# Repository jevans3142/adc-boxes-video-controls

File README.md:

# ADC Theatre - Control Boxes Video Switchers

This repository hosts the hardware (in the form of KiCad schematics, PCB layouts, 3D print files, and metalwork cutting outines) and 
firmware (in the form of C code) of the [ADC Theatre's](https://www.adctheatre.com) Control Boxes Video Switchers. These are a pair of control panels mounted in each control box which 
provides remote control of a Blackmagic Design Videohub SDI switcher via Ethernet.

## Features
* Each panel controls a single video output on the switcher, with six sources 
* Panels have steel panel fronts and backs, with a 3D printed case around them
* An additional steel plate mounts the assembly to a VESA mount behind a screen to drop the panel neatly under the screen

## Configuration

Although some things such as number of buttons etc are fixed in hardware, some aspects can be customised via a text file 
on a microSD card read at boot. This provides the ADC with the ability to reconfigure for example which sources are availible on the panel without having to recompile firmware (as long as the physical buttons are relabeled of course!)

Items which can be configured: 
* Which router inputs are used as sources for each of the destinations 
* IP address of the router

## Compilation
The microcontroller used is an ESP32 on an Olimex ESP32-PoE-ISO board. After standard installation of the esp-idf FreeRTOS toolchain, currently building on v5.1.1 as a stable version with the configuration included in the src folder (ie. when building do not run the idf.py set-target esp32 command as directed in the esp-idf Getting Started instructions to set up the default build config - just go straight to idf.py build)

## Hardware
Each panel requires the following components: 
* A Olimex ESP32-PoE-ISO board
* A custom PCB 'main-board' to break out the button/LED connections
* A 3D printed case, which various heat-fit standoffs need to be sunk into to mount the main-board PCB and front/back panels
* A front panel consisting of a laser cut steel panel with buttons/LEDs mounted in; this also has a label strip. A 3D printed version is in the repo, but there is an off-the-shelf part that can be used too 
* A back panel with another 3D printed part used as an SD card cover
* A VESA mounting steel plate 

## Copyright
Copyright (c) 2021-2024 John Evans and contributors.
The ADC Control Boxes Video Switcher hardware and firmware is released under Version 3 of the GNU General Public License.
See the LICENSE file for full details.

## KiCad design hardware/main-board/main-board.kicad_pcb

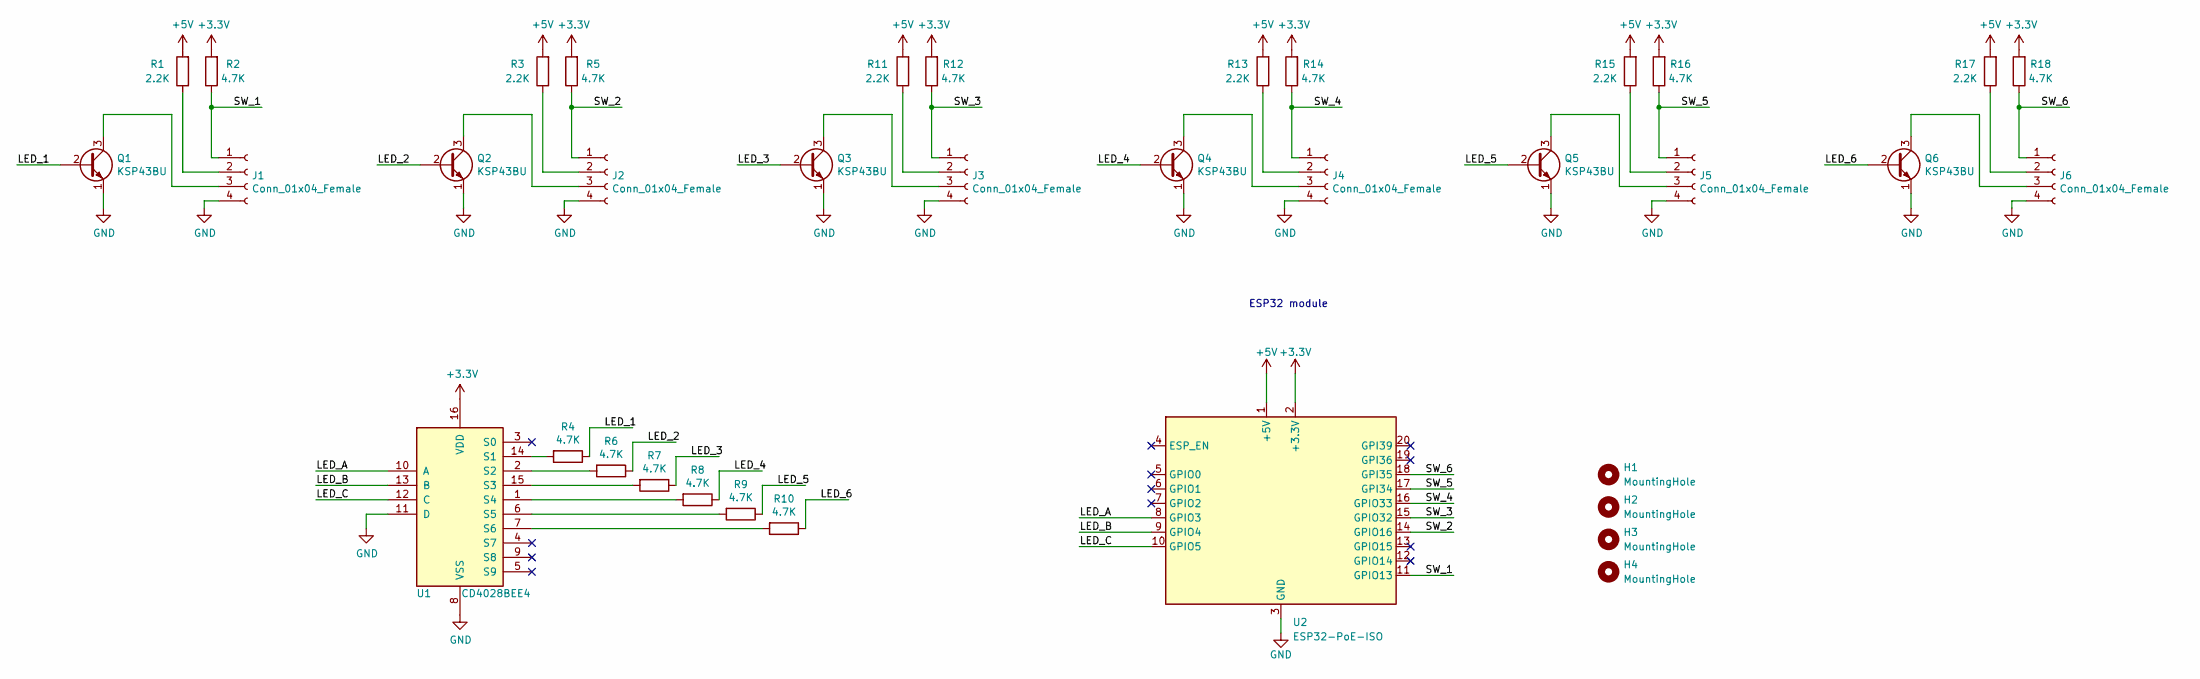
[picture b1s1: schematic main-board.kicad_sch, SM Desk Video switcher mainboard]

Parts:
H1, H2, H3, H4: MountingHole; MountingHole_3.2mm_M3
J1, J2, J3, J4, J5, J6: Conn_01x04_Female; PinHeader_1x04_P2.54mm_Vertical
Q1, Q2, Q3, Q4, Q5, Q6: KSP43BU; TO-92_Inline_Wide
R1, R3, R11, R13, R15, R17: 2.2K; R_Axial_DIN0207_L6.3mm_D2.5mm_P10.16mm_Horizontal
R2, R4, R5, R6, R7, R8, R9, R10, R12, R14, R16, R18: 4.7K; R_Axial_DIN0207_L6.3mm_D2.5mm_P10.16mm_Horizontal
U1: CD4028BEE4; DIP-16_W7.62mm_Socket
U2: ESP32-PoE-ISO; Olimex_ESP32_PoE_ISO

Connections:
+3V3: R2.2, R5.2, R12.2, R14.2, R16.2, R18.2, U1.16 (VDD), U2.2 (+3.3V)
+5V: R1.2, R3.2, R11.2, R13.2, R15.2, R17.2, U2.1 (+5V)
/LED_1: Q1.2 (B), R4.1
/LED_2: Q2.2 (B), R6.1
/LED_3: Q3.2 (B), R7.1
/LED_4: Q4.2 (B), R8.1
/LED_5: Q5.2 (B), R9.1
/LED_6: Q6.2 (B), R10.1
/LED_A: U1.10 (A), U2.8 (GPIO3)
/LED_B: U1.13 (B), U2.9 (GPIO4)
/LED_C: U1.12 (C), U2.10 (GPIO5)
/SW_1: J1.1, R2.1, U2.11 (GPIO13)
/SW_2: J2.1, R5.1, U2.14 (GPIO16)
/SW_3: J3.1, R12.1, U2.15 (GPIO32)
/SW_4: J4.1, R14.1, U2.16 (GPIO33)
/SW_5: J5.1, R16.1, U2.17 (GPI34)
/SW_6: J6.1, R18.1, U2.18 (GPI35)
GND: J1.4, J2.4, J3.4, J4.4, J5.4, J6.4, Q1.1 (E), Q2.1 (E), Q3.1 (E), Q4.1 (E), Q5.1 (E), Q6.1 (E), U1.8 (VSS), U1.11 (D), U2.3 (GND)
unnamed: J1.2, R1.1
unnamed: J1.3, Q1.3 (C)
unnamed: J2.2, R3.1
unnamed: J2.3, Q2.3 (C)
unnamed: J3.2, R11.1
unnamed: J3.3, Q3.3 (C)
unnamed: J4.2, R13.1
unnamed: J4.3, Q4.3 (C)
unnamed: J5.2, R15.1
unnamed: J5.3, Q5.3 (C)
unnamed: J6.2, R17.1
unnamed: J6.3, Q6.3 (C)
unnamed: R4.2, U1.14 (S1)
unnamed: R6.2, U1.2 (S2)
unnamed: R7.2, U1.15 (S3)
unnamed: R8.2, U1.1 (S4)
unnamed: R9.2, U1.6 (S5)
unnamed: R10.2, U1.7 (S6)

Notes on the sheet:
ESP32 module

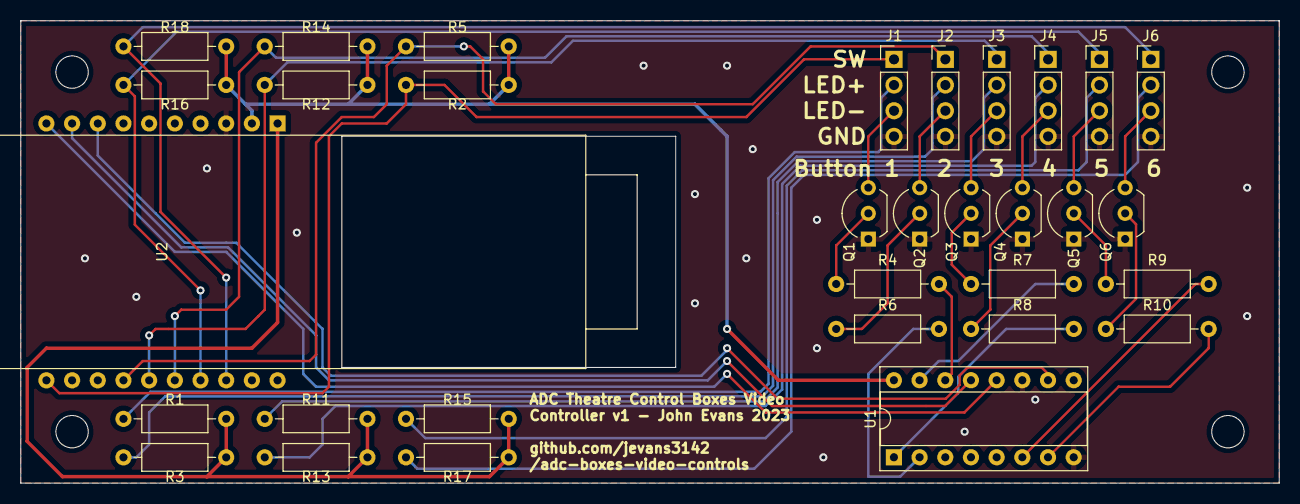
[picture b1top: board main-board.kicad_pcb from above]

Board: 2 copper layers, 124.5 x 45.7 mm, 36 parts (0 on the bottom side), 36 nets.

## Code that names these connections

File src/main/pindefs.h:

// Pin definitions for IO
//-----------------------------------

#ifndef PINDEFS_H_INCLUDED
#define PINDEFS_H_INCLUDED

// Pin defs

#define PIN_SDCARD_CMD 15
#define PIN_SDCARD_CLK 14
#define PIN_SDCARD_DTA 2

#define PIN_PHY_MDC 23
#define PIN_PHY_MDIO 18
#define PIN_PHY_RST -1
#define PIN_PHY_POWER 12

#define PIN_LED_A 3 
#define PIN_LED_B 4 
#define PIN_LED_C 5 

#define PIN_BUTTON_1 13
#define PIN_BUTTON_2 16
#define PIN_BUTTON_3 32
#define PIN_BUTTON_4 33
#define PIN_BUTTON_5 34
#define PIN_BUTTON_6 35

#define PIN_BUTTON_MASK (1ULL << PIN_BUTTON_1) | (1ULL << PIN_BUTTON_2) | (1ULL << PIN_BUTTON_3) | (1ULL << PIN_BUTTON_4) | (1ULL << PIN_BUTTON_5) | (1ULL << PIN_BUTTON_6)

#define PIN_LED_MASK (1ULL << PIN_LED_A) | (1ULL << PIN_LED_B) | (1ULL << PIN_LED_C)  

#endif

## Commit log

2024-06-28 Initial deployment
    Based on SM desk video switcher - initial deployment
2024-06-30 Add TCP keepalives
2024-07-08 Add PCB and 3D printing files
2026-05-16 Correct README file
